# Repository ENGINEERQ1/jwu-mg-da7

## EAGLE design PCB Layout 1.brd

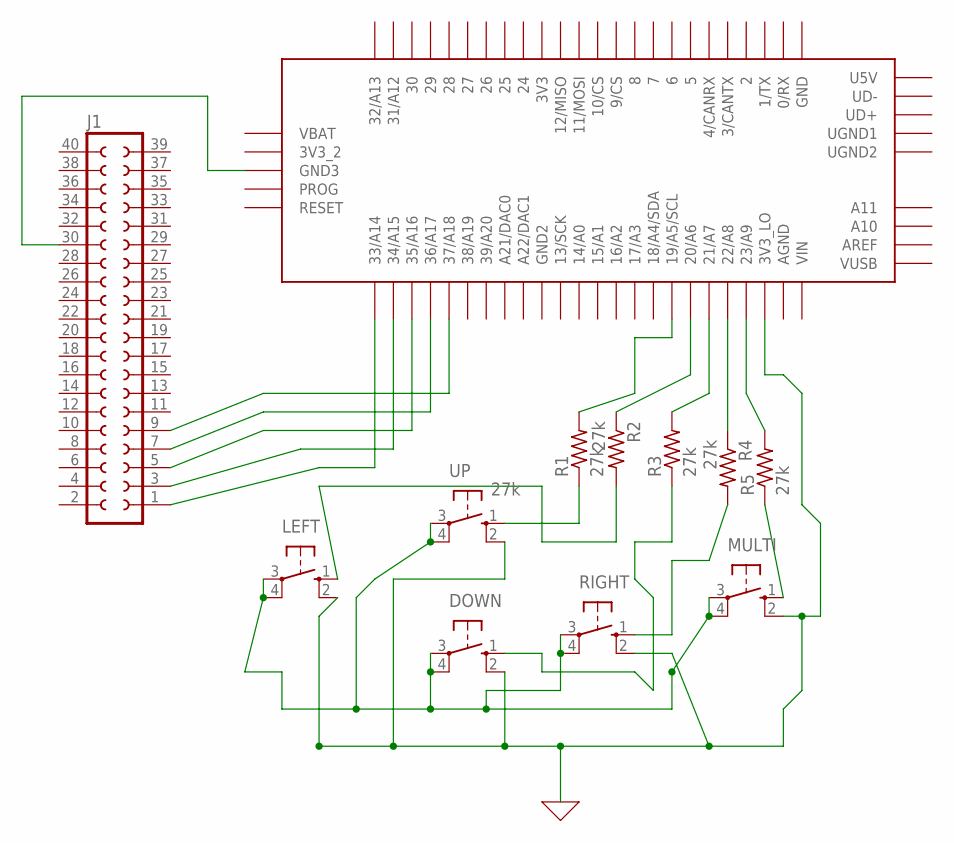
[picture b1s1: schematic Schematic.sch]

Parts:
DOWN: 27k; B3F-10XX
J1: SOCKET-40V; S40V
LEFT: 27k; B3F-10XX
MULTI: 27k; B3F-10XX
R1, R2, R3, R4, R5: 27k; 0204V
RIGHT: 27k; B3F-10XX
U$2: TEENSY_3.5/3.6
UP: 27k; B3F-10XX

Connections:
0: DOWN.2 (S1), DOWN.3, DOWN.4 (P1), LEFT.2 (S1), LEFT.3, LEFT.4 (P1), MULTI.2 (S1), MULTI.3, MULTI.4 (P1), RIGHT.2 (S1), RIGHT.3, RIGHT.4 (P1), U$2.3V3_LO, UP.2 (S1), UP.3, UP.4 (P1)
unnamed: J1.30, U$2.GND3
unnamed: R1.1, UP.1 (S)
unnamed: LEFT.1 (S), R2.2
unnamed: R4.2, RIGHT.1 (S)
unnamed: MULTI.1 (S), R5.1
unnamed: DOWN.1 (S), R3.1
unnamed: R4.1, U$2.22/A8
unnamed: J1.1, U$2.33/A14
unnamed: J1.3, U$2.34/A15
unnamed: J1.5, U$2.35/A16
unnamed: J1.7, U$2.36/A17
unnamed: J1.9, U$2.37/A18
unnamed: R5.2, U$2.23/A9
unnamed: R3.2, U$2.21/A7
unnamed: R2.1, U$2.20/A6
unnamed: R1.2, U$2.19/A5/SCL

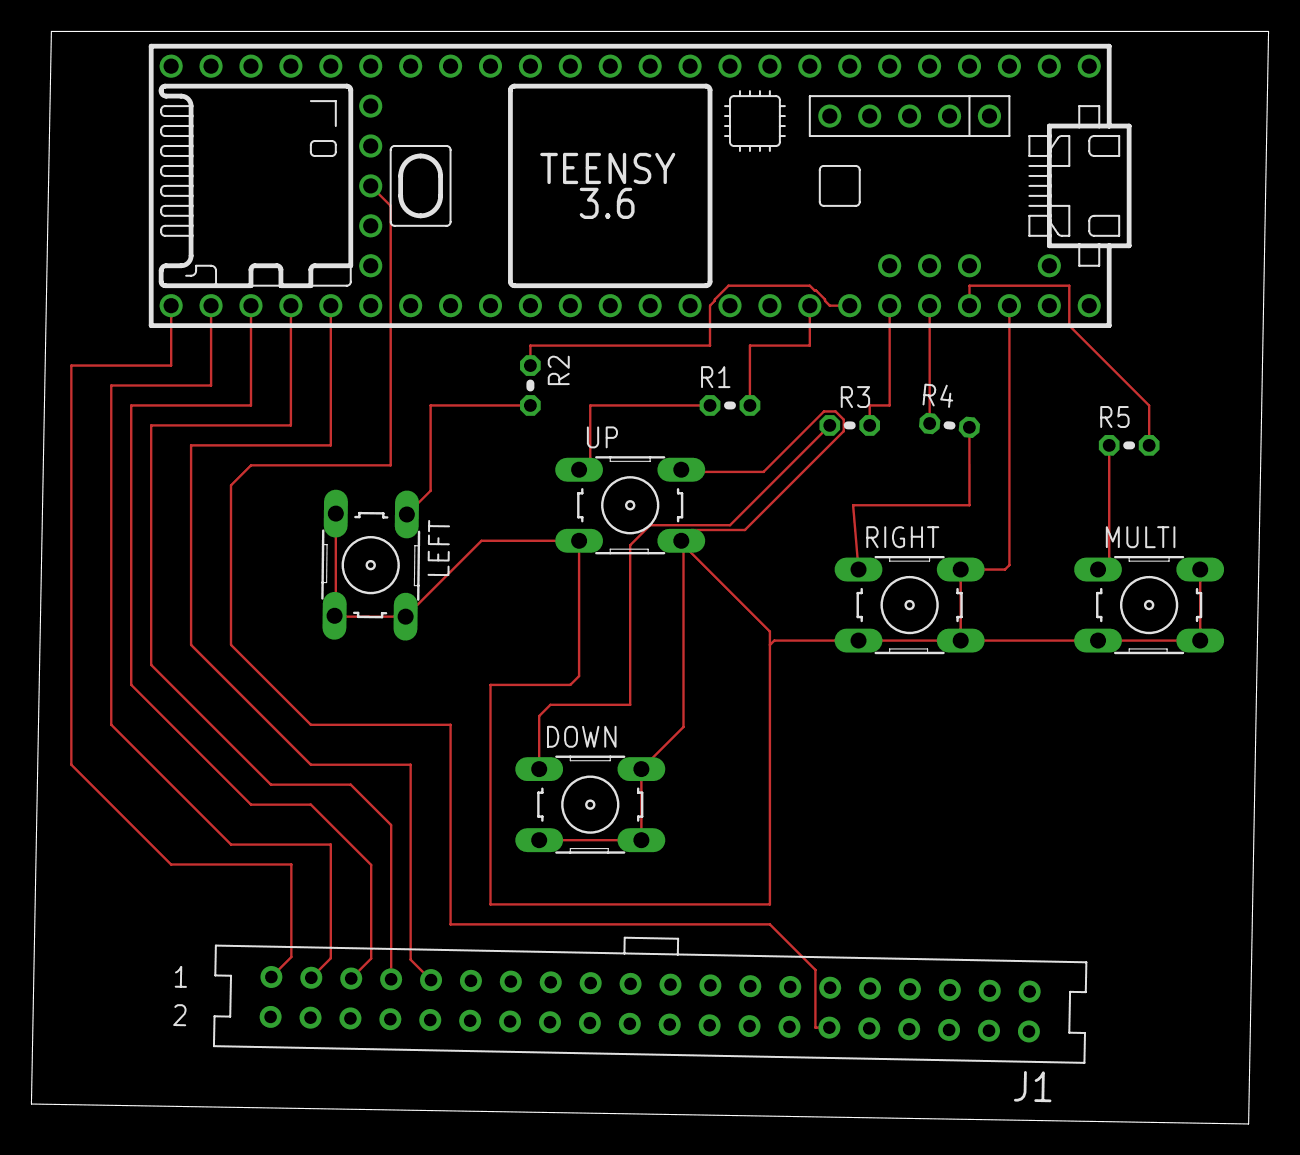
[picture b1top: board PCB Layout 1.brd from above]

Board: 2 copper layers, 78.7 x 69.5 mm, 12 parts (0 on the bottom side), 17 nets.
